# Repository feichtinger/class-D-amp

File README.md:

# class-D amplifier

This is a construction kit for a neat 2x5W class-D stereo amplifier.

## purpose
This kit was developed together with Thomas Voglhuber at the [Insitute for Microelectronics and Microsensors](http://www.ime.jku.at) at the Johannes Kepler University.

It is especially designed to be easy to solder even for beginners and may be used for workshops with students or trainees.

The kit provides all components (including power supply and a pair of speakers) that are necessary to build a cute homemade stereo system.

## technical details
The circuit is based on a TPA3125D2 chip with only a view minor extensions such as volume controll and a power switch. Due to the digital operation principle the amplifier reaches a good performance with very low power disspation. Although the circuit was designed for 16 Ohm speakers the chip and the circuit can easily handle even 4 Ohm speakers to gain more output power without the need of a heatsink.

The schematic and PCB layout was made using [KiCad](http://www.kicad-pcb.org/display/KICAD/KiCad+EDA+Software+Suite). The PCB layout was designed with respect to the basic rules of power electronics such as separation of power and signal current traces and keeping high frequency current traces as short as possible.

This is open hardware, so feel free to build, change and improve things!

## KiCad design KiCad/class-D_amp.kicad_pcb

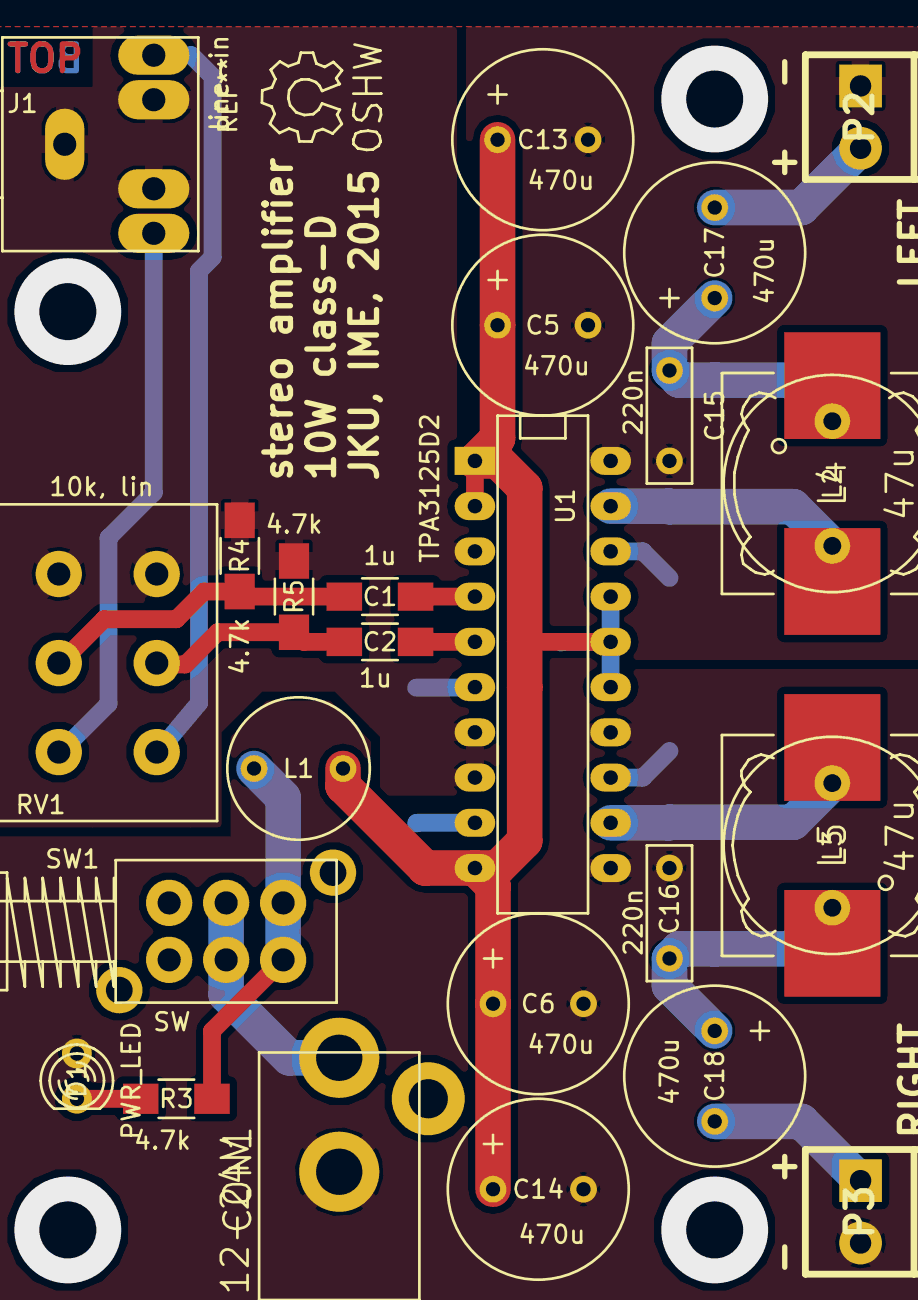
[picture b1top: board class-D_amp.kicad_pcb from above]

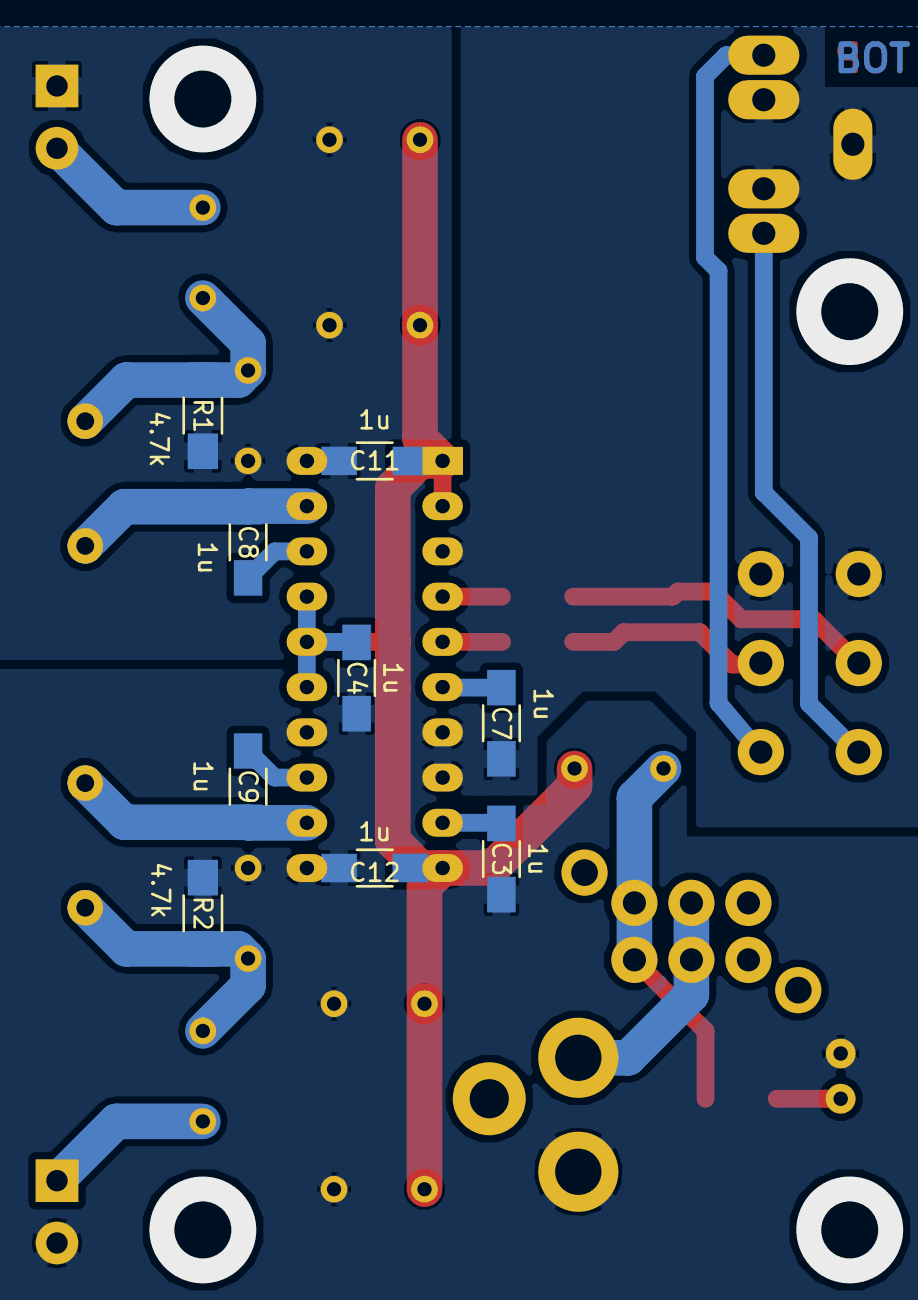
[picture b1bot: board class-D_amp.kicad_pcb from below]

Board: 2 copper layers, 35 parts (9 on the bottom side), 21 nets.

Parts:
C1, C2, C3, C4, C7, C8, C9, C11, C12: 1u; C_1206_HandSoldering
C5, C6, C13, C14, C17, C18: 470u; Elko_vert_20x10mm_RM5_CopperClear
C15, C16: 220n; Capacitor7x2.5RM5
CON1: 12-24V; DC-conn
D1: PWR_LED; LED-3MM
J1: line-in; stereo_jack_3.5mm
L1: 330u; Neosid_Inductor_Sd8
L2, L3: 33u; Choke_SMD_12x12mm_h4.5mm_handsolder
L4, L5: 47u; inductor_d12.5_RM7
P2: LEFT; pt_1,5-2-3,5-h
P3: RIGHT; pt_1,5-2-3,5-h
R1, R2, R3, R4, R5: 4.7k; R_1206_HandSoldering
RV1: 10k, lin; Potentiometer_double_15mm
SW1: SW; DPDT_push_switch
U1: TPA3125D2; DIP-20__300_ELL

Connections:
GND: C3.2, C4.2, C5.2, C6.2, C7.2, C11.2, C12.2, C13.2, C14.2, C15.2, C16.2, CON1.2, D1.1, J1.1, J1.4, J1.5, P2.1, P3.2, R1.2, R2.2, R4.2, R5.2, RV1.3, RV1.6, U1.3, U1.7, U1.8, U1.11, U1.14, U1.20
unnamed: C1.1, U1.4
unnamed: C1.2, R4.1, RV1.2
unnamed: C2.1, U1.5
unnamed: C2.2, R5.1, RV1.5
unnamed: C3.1, U1.9
unnamed: C7.1, U1.6
unnamed: C8.1, L2.2, L4.2, U1.19
unnamed: C8.2, U1.18
unnamed: C9.1, L3.2, L5.2, U1.12
unnamed: C9.2, U1.13
unnamed: C15.1, C17.1, L2.1, L4.1, R1.1
unnamed: C16.1, C18.1, L3.1, L5.1, R2.1
unnamed: C17.2, P2.2
unnamed: C18.2, P3.1
unnamed: CON1.1, SW1.2, SW1.5
unnamed: D1.2, R3.2
unnamed: J1.2, RV1.1
unnamed: J1.3, RV1.4
unnamed: L1.2, R3.1, SW1.3, SW1.6
VCC: C4.1, C5.1, C6.1, C11.1, C12.1, C13.1, C14.1, L1.1, U1.1, U1.2, U1.10, U1.15, U1.16, U1.17
